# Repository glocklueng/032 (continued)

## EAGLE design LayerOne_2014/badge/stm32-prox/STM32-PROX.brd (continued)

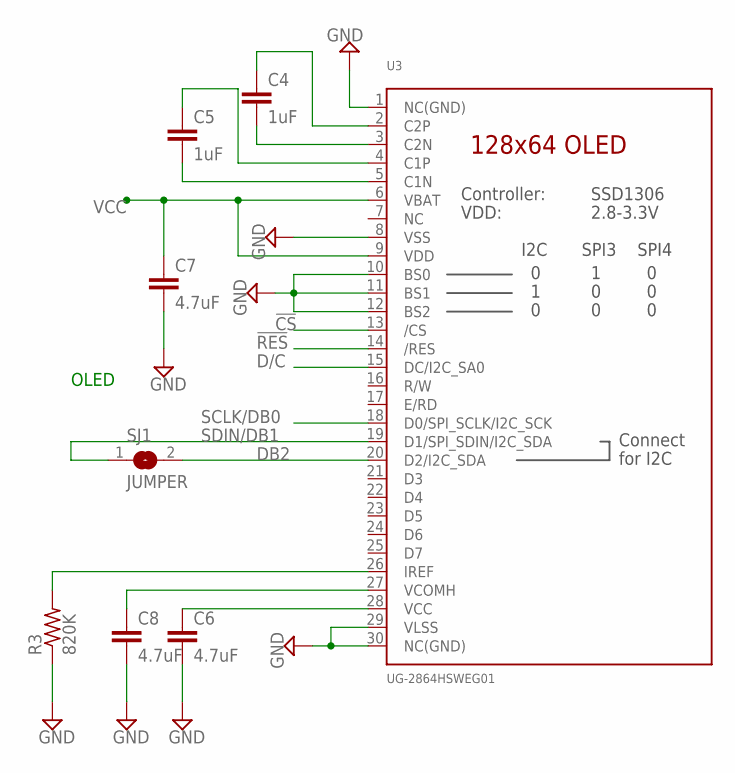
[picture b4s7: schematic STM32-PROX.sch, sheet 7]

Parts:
C4, C5: 1uF; 0805; MPN CC0805ZRY5V8BB105; DIGIKEY 311-1358-1-ND
C6, C7, C8: 4.7uF; 0805; MPN CL21A475KOFNNNE; DIGIKEY 1276-1065-1-ND
R3: 820K; RLC_0603; MPN RC0603JR-07820KL; DIGIKEY 311-820KGRTR-ND
SJ1: JUMPER; SOLDERJUMPER_REFLOW; MPN NONE
U3: UG-2864HSWEG01; MICROBUILDER_UG-2864HSWEG01_0.96IN_WRAPAROUND; PARTNO *

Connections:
!CS: U3.13 (/CS); also elsewhere on the board
!RES: U3.14 (/RES); also elsewhere on the board
D/C: U3.15 (DC/I2C_SA0); also elsewhere on the board
DB2: SJ1.2, U3.20 (D2/I2C_SDA)
GND: C6.2, C7.2, C8.2, R3.1, U3.1 (NC(GND)), U3.8 (VSS), U3.10 (BS0), U3.11 (BS1), U3.12 (BS2), U3.29 (VLSS), U3.30 (NC(GND)); also elsewhere on the board
unnamed: C4.1, U3.2 (C2P)
unnamed: C4.2, U3.3 (C2N)
unnamed: C5.1, U3.4 (C1P)
unnamed: C5.2, U3.5 (C1N)
unnamed: C8.1, U3.27 (VCOMH)
unnamed: C6.1, U3.28 (VCC)
unnamed: R3.2, U3.26 (IREF)
SCLK/DB0: U3.18 (D0/SPI_SCLK/I2C_SCK); also elsewhere on the board
SDIN/DB1: SJ1.1, U3.19 (D1/SPI_SDIN/I2C_SDA); also elsewhere on the board
VCC: C7.1, U3.6 (VBAT), U3.9 (VDD); also elsewhere on the board

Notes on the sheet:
OLED

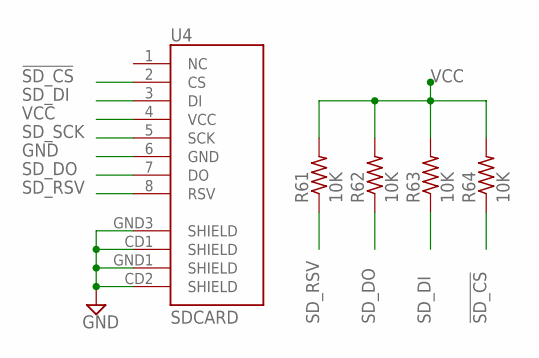
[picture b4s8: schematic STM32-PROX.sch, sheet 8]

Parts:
R61, R62, R63, R64: 10K; RLC_0603; MPN RMCF0603JT10K0; DIGIKEY RMCF0603JT10K0CT-ND
U4: SDCARD; MICRO-SD-SOCKET-PP; PARTNO *

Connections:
!SD_CS: R64.1, U4.2 (CS); also elsewhere on the board
GND: U4.6 (GND), U4.CD1 (SHIELD), U4.CD2 (SHIELD), U4.GND1 (SHIELD), U4.GND3 (SHIELD); also elsewhere on the board
SD_DI: R63.1, U4.3 (DI); also elsewhere on the board
SD_DO: R62.1, U4.7 (DO); also elsewhere on the board
SD_RSV: R61.1, U4.8 (RSV)
SD_SCK: U4.5 (SCK); also elsewhere on the board
VCC: R61.2, R62.2, R63.2, R64.2, U4.4 (VCC); also elsewhere on the board

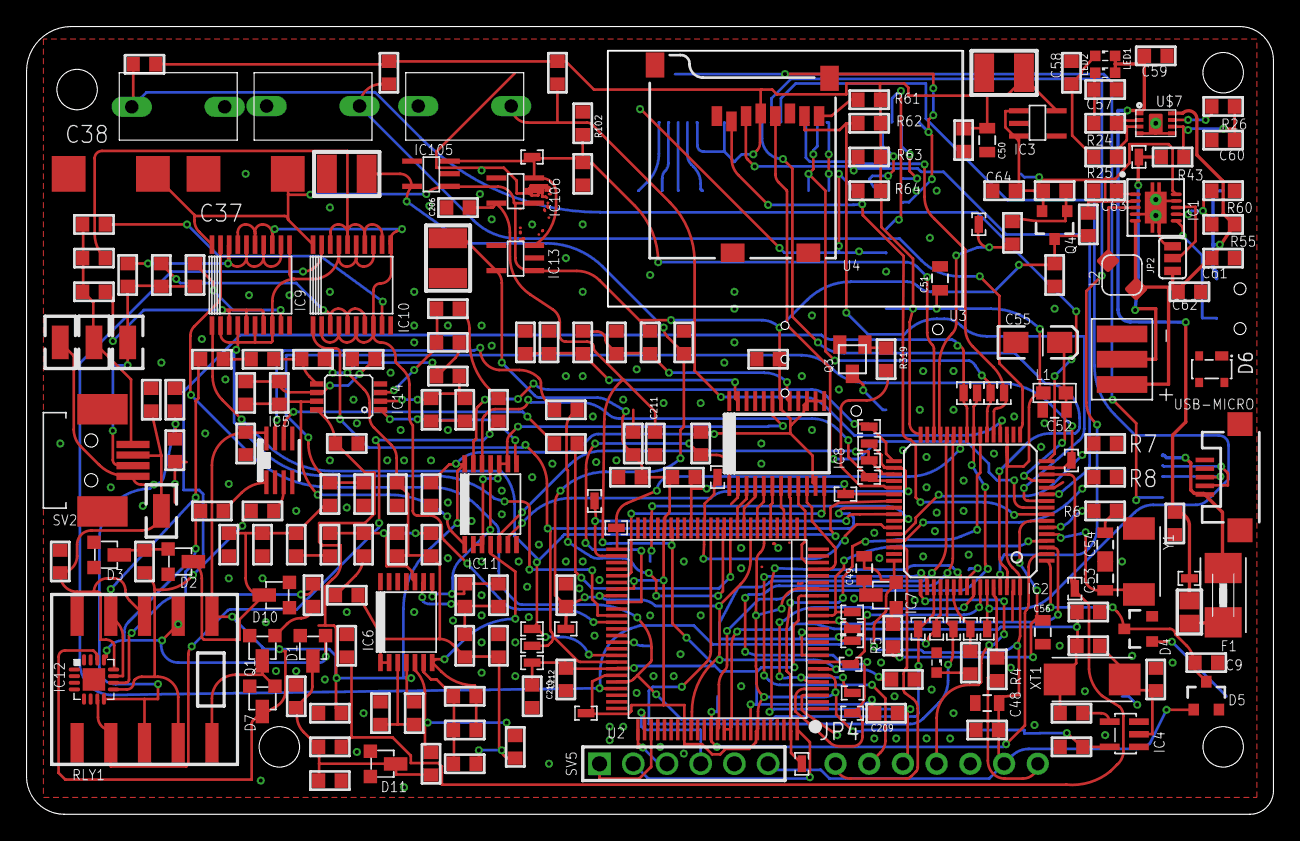
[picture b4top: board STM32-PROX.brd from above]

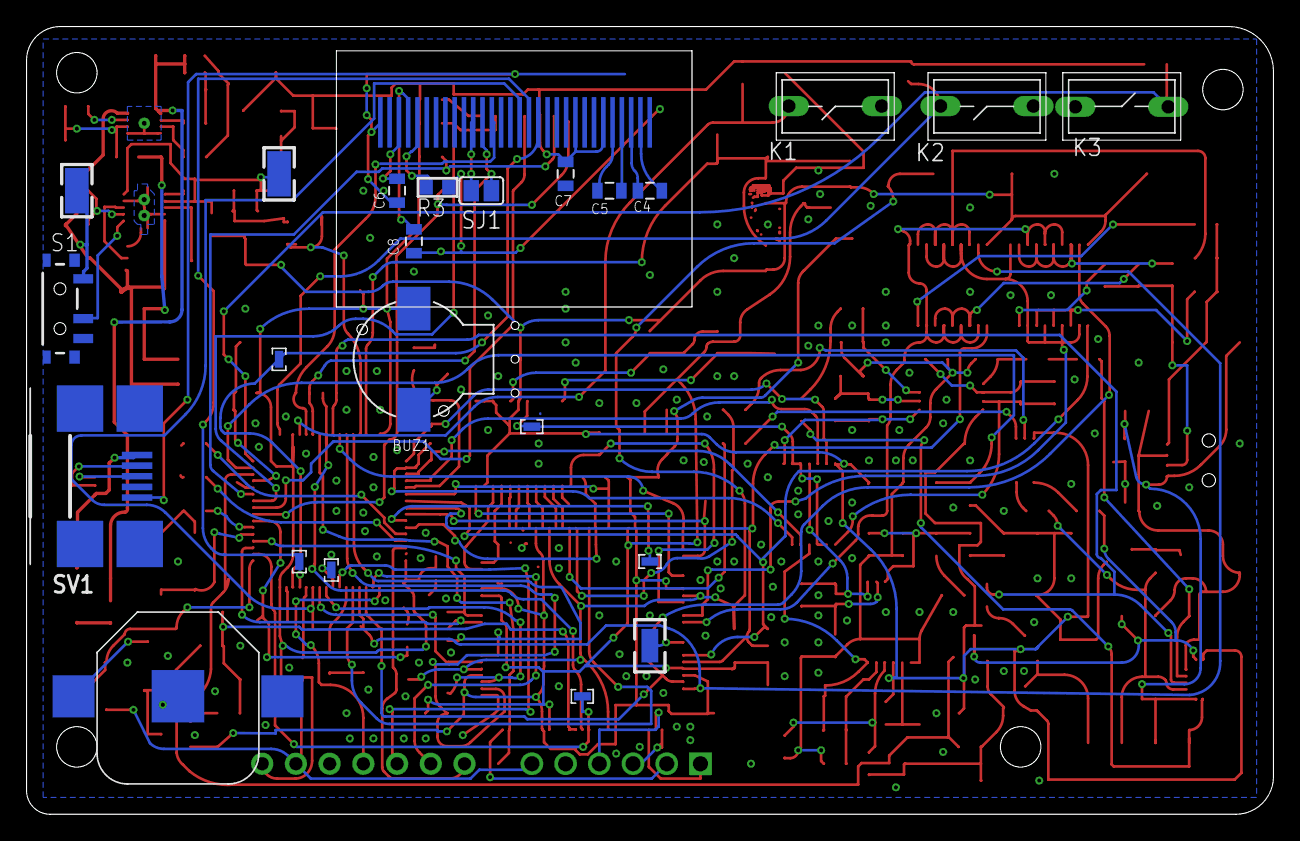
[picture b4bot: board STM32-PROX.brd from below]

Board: 2 copper layers, 94.0 x 59.4 mm, 250 parts (23 on the bottom side), 163 nets.

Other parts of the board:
U$1, U$2, U$4, U$6: STAND-OFF-TIGHT
U$11, U$12, U$13: L1LOGO

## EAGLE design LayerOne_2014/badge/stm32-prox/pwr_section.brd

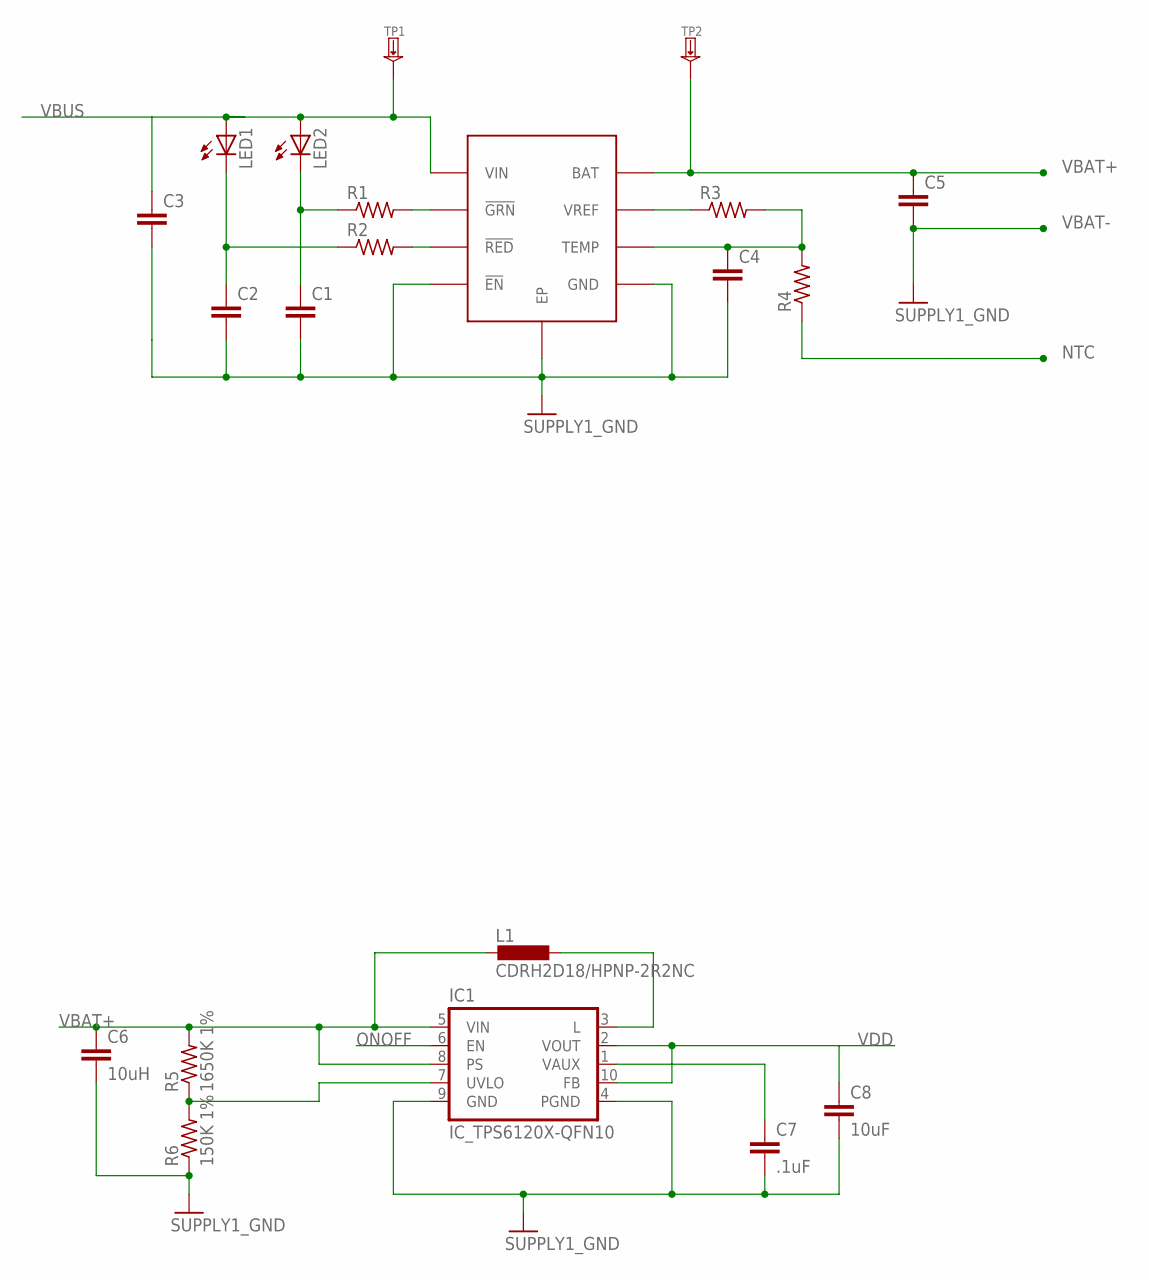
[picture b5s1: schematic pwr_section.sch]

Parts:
C1, C2, C3, C4, C5: SPARKFUN_CAP0603-CAP; SPARKFUN_0603-CAP
C6: 10uH; SPARKFUN_0603-CAP
C7: .1uF; SPARKFUN_0603-CAP
C8: 10uF; SPARKFUN_0603-CAP
IC1: IC_TPS6120X-QFN10; QFN-10
L1: CDRH2D18/HPNP-2R2NC; CDRH2D18
LED1, LED2: LED_LEDCHIP-LED0603; LED_CHIP-LED0603
R1, R2, R3, R4: RCL_R-US_R0603; RCL_R0603
R5: 1650K 1%; RCL_R0603
R6: 150K 1%; RCL_R0603
TP1, TP2: --MERGED_TESTPADKEYSTONE-SMD; --MERGED_KEYSTONE-SMD-TESTPOINT-5015
U$1: MC34674; UDFN-EP

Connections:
GND: C1.2, C2.2, C3.2, C4.2, C6.2, R6.1, U$1.4 (!EN), U$1.5 (GND), U$1.9 (EP)
unnamed: C1.1, LED2.C, R1.1
unnamed: R1.2, U$1.2 (!GRN)
unnamed: C2.1, LED1.C, R2.1
unnamed: R2.2, U$1.3 (!RED)
unnamed: C7.1, IC1.1 (VAUX)
unnamed: IC1.3 (L), L1.P$2 (2)
unnamed: R3.1, U$1.7 (VREF)
unnamed: C4.1, R3.2, R4.2, U$1.6 (TEMP)
unnamed: IC1.7 (UVLO), R5.1, R6.2
NTC: R4.1
ONOFF: IC1.6 (EN)
PGND: C7.2, C8.2, IC1.4 (PGND), IC1.9 (GND)
VBAT+: C5.1, C6.1, IC1.5 (VIN), IC1.8 (PS), L1.P$1 (1), R5.2, TP2.1, U$1.8 (BAT)
VBAT-: C5.2
VBUS: C3.1, LED1.A, LED2.A, TP1.1, U$1.1 (VIN)
VDD: C8.1, IC1.2 (VOUT), IC1.10 (FB)

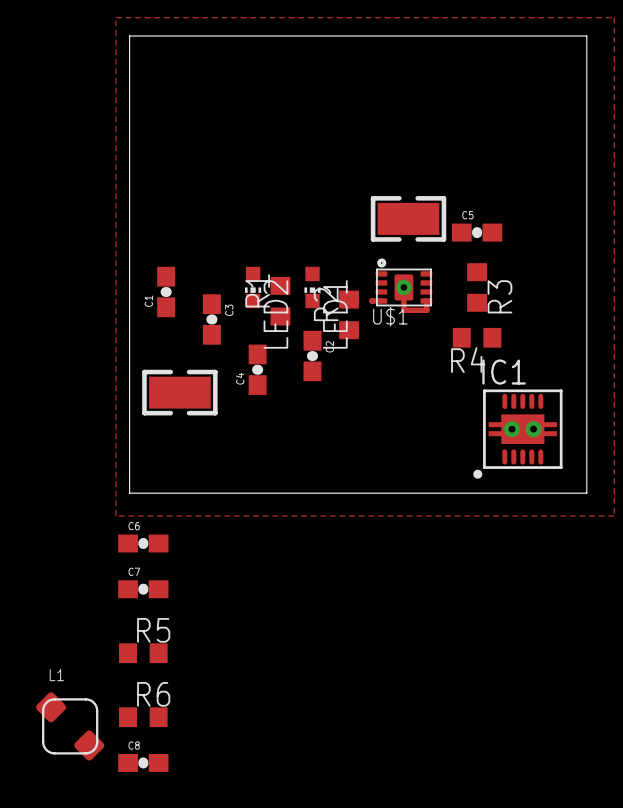
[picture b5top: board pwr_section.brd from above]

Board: 2 copper layers, 25.4 x 25.4 mm, 21 parts (0 on the bottom side), 14 nets.

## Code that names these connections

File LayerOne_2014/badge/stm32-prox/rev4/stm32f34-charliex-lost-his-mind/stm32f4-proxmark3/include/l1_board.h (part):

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
// SPI PINS ARM->FPGA (PROGRAMS & CONFIGURES FPGA)
#define FPGA_DOUT_PORT                  GPIOC
#define FPGA_DOUT_PIN                   GPIO_Pin_11				//output ( reconfigure this to be PCK0)

#define	FPGA_DIN_PORT			GPIOA
#define FPGA_DIN_PIN                    GPIO_Pin_9				//output

#define	FPGA_CCLK_PORT			GPIOA
#define FPGA_CCLK_PIN                   GPIO_Pin_8				//output

#define	FPGA_NPROGRAM_PORT		GPIOA
#define FPGA_NPROGRAM_PIN               GPIO_Pin_7				//output


//OLED
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// Switches

#if BOARD_REVISION == 3
#define SW_K1_PORT                     GPIOB
#else
#define SW_K1_PORT                     GPIOA
#endif

#define SW_K2_PORT                     GPIOA
#define SW_K3_PORT                     GPIOA

#define	RCC_APB2Periph_GPIO_SW		   RCC_APB2Periph_GPIOA
#if BOARD_REVISION == 3
#define SW_K1_PIN                      GPIO_Pin_9				// input, pulldown
#else
#define SW_K1_PIN                      GPIO_Pin_4				// input, pulldown
#endif

#define SW_K2_PIN                      GPIO_Pin_3				// input, pulldown
#define SW_K3_PIN                      GPIO_Pin_2				// input, pulldown

// USB
#if BOARD_REVISION == 3
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#define GPIO_SW_PORTSOURCE            GPIO_PortSourceGPIOA      		// PA

#if BOARD_REVISION == 3
#define GPIO_SW_K1_PINSOURCE          GPIO_PinSource9     			// PB9
#define GPIO_SW_K2_PINSOURCE   	      GPIO_PinSource3     			// PA4
#else
#define GPIO_SW_K1_PINSOURCE          GPIO_PinSource4     			// PA4
#define GPIO_SW_K2_PINSOURCE   	      GPIO_PinSource2     			// PA4
#endif

#define GPIO_SW_K1_EXTI_Line          EXTI_Line0          

// Ampl Lo/Hi
#define AMPL_HI_PIN                    GPIO_Pin_1				// input analog
#define AMPL_LO_PIN                    GPIO_Pin_0				// input analog

#define ADC_AIN_CHANNEL                ADC_Channel_1             		// PA1

#ifdef CS_PIN
#define GPIOA_OUTPUTS_2MHZ_PP_MASK		( CS_PIN | FPGA_NPROGRAM_PIN |SDIN_DB1_PIN | SCLK_DB0_PIN )
#else
#define GPIOA_OUTPUTS_2MHZ_PP_MASK		( FPGA_NPROGRAM_PIN |SDIN_DB1_PIN | SCLK_DB0_PIN )
#endif

#if BOARD_REVISION == 3
#define GPIOA_OUTPUTS_50MHZ_PP_MASK		( FPGA_DOUT_PIN  | FPGA_DIN_PIN | FPGA_CCLK_PIN | SDIN_DB1_PIN | SCLK_DB0_PIN )
#else
#define GPIOA_OUTPUTS_50MHZ_PP_MASK		( FPGA_DOUT_PIN  | FPGA_DIN_PIN | FPGA_CCLK_PIN | USB_DISCONNECT_PIN   | SDIN_DB1_PIN | SCLK_DB0_PIN )
#endif

//#define GPIOA_OUTPUTS_50MHZ_OD_MASK		( USB_DISCONNECT_PIN )
#define GPIOA_INPUT_FLOAT_MASK			( SW_K3_PIN  )
#if BOARD_REVISION == 3
#define GPIOA_INPUT_PULLDOWN_MASK		(  SW_K2_PIN  )
#else
#define GPIOA_INPUT_PULLDOWN_MASK		( SW_K1_PIN | SW_K2_PIN )
#endif
#define GPIOA_ANALOG_MASK			( AMPL_HI_PIN | AMPL_LO_PIN  )
#define GPIOA_DEFAULT_LOW_MASK			( GPIOA_OUTPUTS_2MHZ_PP_MASK | GPIOA_OUTPUTS_50MHZ_PP_MASK )

/* End Section GPIOA */
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#	define MUXSEL_PORT              GPIOB
#endif

#define	MUXSEL_HIPKD_PORT		MUXSEL_PORT
#define	MUXSEL_LOPKD_PORT		MUXSEL_PORT

#define	MUXSEL_HIRAW_PORT		GPIOB
#define	MUXSEL_LORAW_PORT		GPIOB



#if BOARD_REVISION == 3
#define MUXSEL_HIPKD_PIN                GPIO_Pin_9			        //output
#define MUXSEL_LOPKD_PIN                GPIO_Pin_8			        //output
#else
#define MUXSEL_HIPKD_PIN                GPIO_Pin_15			        //output
#define MUXSEL_LOPKD_PIN                GPIO_Pin_14			        //output
#endif


#if BOARD_REVISION == 3
//PORTB
#define MUXSEL_HIRAW_PIN                GPIO_Pin_2			        //output
#define MUXSEL_LORAW_PIN                GPIO_Pin_1			        //output
#else
#define MUXSEL_HIRAW_PIN                GPIO_Pin_13			        //output
#define MUXSEL_LORAW_PIN                GPIO_Pin_12			        //output
#endif

// FPGA Power On
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#define FPGAON_PIN                      GPIO_Pin_11				//output

// USB Power On
#define	NVDD_ON_PORT			GPIOB
#define NVDD_ON_PIN                     GPIO_Pin_10				//output

// FPGA DONE
#define FPGA_DONE_PORT                  GPIOB
#define FPGA_DONE_PIN                   GPIO_Pin_0				// input


// OLED
#if BOARD_REVISION == 3
#define OLED_PORT                	GPIOB
#define RES_PIN                         GPIO_Pin_8               		// inverted output
#define DC_PIN                          GPIO_Pin_7				// output
#else
#define OLED_PORT                	GPIOB
#define OLED_CS_PORT                	GPIOB
#define CS_PIN                          GPIO_Pin_9               		// inverted output
#define RES_PIN                         GPIO_Pin_8               		// inverted output
#define DC_PIN                          GPIO_Pin_7				// output
#endif

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#if BOARD_REVISION == 3

#define SSP_PORT	                GPIOB
#define SSP_DIN_PORT			GPIOB
#define SSP_DIN_PIN                     GPIO_Pin_15				// input(OUTPUT)	
#define SSP_DOUT_PORT			GPIOB
#define SSP_DOUT_PIN                    GPIO_Pin_14				// output
#define SSP_CLK_PORT			GPIOB
#define SSP_CLK_PIN                     GPIO_Pin_13			        // input
#define SSP_FRAME_PORT			GPIOB
#define SSP_FRAME_PIN                   GPIO_Pin_12				// input

#else

#define SSP_PORT	                GPIOB
#define SSP_DIN_PORT			GPIOB

#define SSP_DIN_PIN                     GPIO_Pin_6				// input(OUTPUT)	
#define SSP_DOUT_PORT			GPIOB
#define SSP_DOUT_PIN                    GPIO_Pin_5				// output
#define SSP_CLK_PORT			GPIOB
#define SSP_CLK_PIN                     GPIO_Pin_2			        // input
#define SSP_FRAME_PORT			GPIOB
#define SSP_FRAME_PIN                   GPIO_Pin_1				// input

#endif

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//@todo: USB_DISCONNECT_PIN
#if BOARD_REVISION == 3

#define GPIOB_OUTPUTS_2MHZ_PP_MASK		( DC_PIN | RES_PIN | USB_DISCONNECT_PIN |				\
						CS_PIN | FPGAON_PIN  | MUXSEL_HIRAW_PIN | MUXSEL_LORAW_PIN )
#else
#define GPIOB_OUTPUTS_2MHZ_PP_MASK		( DC_PIN | RES_PIN | 				\
						CS_PIN | FPGAON_PIN  | MUXSEL_HIPKD_PIN | 	\
						MUXSEL_LOPKD_PIN |MUXSEL_HIRAW_PIN | MUXSEL_LORAW_PIN )
#endif

//#define GPIOB_OUTPUTS_10MHZ_PP_MASK		( )
#define GPIOB_OUTPUTS_50MHZ_PP_MASK		( NVDD_ON_PIN  )
//#define GPIOB_OUTPUTS_50MHZ_OD_MASK		( USB_DISCONNECT_PIN )

//#define GPIOB_INPUT_FLOAT_MASK		( SSP_CLK_PIN )
#define GPIOB_INPUT_PULLUP_MASK			( FPGA_DONE_PIN ) 

#if BOARD_REVISION == 3
#define GPIOB_INPUT_PULLDOWN_MASK		( SW_K1_PIN | SSP_FRAME_PIN | SSP_DIN_PIN |SSP_DOUT_PIN | SSP_CLK_PIN ) // Might want to make these float
#else
#define GPIOB_INPUT_PULLDOWN_MASK		( SSP_FRAME_PIN | SSP_DIN_PIN |SSP_DOUT_PIN | SSP_CLK_PIN ) // Might want to make these float
#endif

//#define GPIOB_ANALOG_MASK			( )
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#define MOSI_PORT                      GPIOC
#define MOSI_PIN                       GPIO_Pin_14				// output to fpga

#define SPCK_PORT                      GPIOC
#define SPCK_PIN                       GPIO_Pin_13				// output to fpga

#define NCS_PORT                       GPIOC
#define NCS_PIN                        GPIO_Pin_12				// output to fpga

#if BOARD_REVISION != 3
// Output Enables (these aren't supposed to be on the ARM) !!
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#endif

// FPGA_NINIT
#define FPGA_NINIT_PORT                 GPIOC
#define FPGA_NINIT_PIN                  GPIO_Pin_7			        // input, pullup

// Speaker
#define SPEAKER_PORT                    GPIOC
#define SPEAKER_PIN                     GPIO_Pin_6                              // output

// Relay control
#define RELAY_PORT                      GPIOC
#define RELAY_PIN                       GPIO_Pin_5

// PCKO
#define PCK0_PORT			GPIOC	
#define PCK0_PIN			GPIO_Pin_4				// output clock for FPGA/SSP 24Mhz clock

// SD-CARD
#define SDCARD_PORT                    GPIOC
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#define SDCS_PIN                       GPIO_Pin_0				// output

#if BOARD_REVISION == 3
#define GPIOC_OUTPUTS_2MHZ_PP_MASK		(MUXSEL_HIPKD_PIN  | MUXSEL_LOPKD_PIN | RELAY_PIN |SDDO_PIN | SDCS_PIN)
#else
#define GPIOC_OUTPUTS_2MHZ_PP_MASK		(   |SDDO_PIN | SDCS_PIN)

#endif

#define GPIOC_OUTPUTS_10MHZ_PP_MASK		( SPEAKER_PIN | SDSCK_PIN | NCS_PIN | MOSI_PIN |SPCK_PIN )
#define GPIOC_OUTPUTS_50MHZ_PP_MASK		( PCK0_PIN   )

#if BOARD_REVISION == 3
#define GPIOC_INPUT_FLOAT_MASK          ( SDDI_PIN | MISO_PIN )
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#define GPIOC_INPUT_FLOAT_MASK          ( OE4_PIN | OE3_PIN | OE2_PIN | OE1_PIN | SDDI_PIN | MISO_PIN )
#endif

#define GPIOC_INPUT_PULLUP_MASK			( FPGA_NINIT_PIN )

#if BOARD_REVISION == 3
#define GPIOC_ANALOG_MASK				( GPIO_Pin_4 | GPIO_Pin_3 )
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#define LED_PORT                        GPIOD
#define LED_PIN                         GPIO_Pin_2                              // output
#define RCC_APB2Periph_GPIO_LED         RCC_APB2Periph_GPIOD      		// PD
// PD0/PD1 XTAL



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
// aliases for proxmark3

#define				GPIO_MUXSEL_HIPKD_PIN	MUXSEL_HIPKD_PIN
#define				GPIO_MUXSEL_LOPKD_PIN	MUXSEL_LOPKD_PIN
#define				GPIO_MUXSEL_HIRAW_PIN	MUXSEL_HIRAW_PIN
#define				GPIO_MUXSEL_LORAW_PIN	MUXSEL_LORAW_PIN

#define				GPIO_MUXSEL_HIPKD_PORT	MUXSEL_HIPKD_PORT
#define				GPIO_MUXSEL_LOPKD_PORT	MUXSEL_LOPKD_PORT
#define				GPIO_MUXSEL_HIRAW_PORT	MUXSEL_HIRAW_PORT
#define				GPIO_MUXSEL_LORAW_PORT	MUXSEL_LORAW_PORT

// only one led
#define				GPIO_LED_A_PIN			LED_PIN
#define				GPIO_LED_B_PIN			LED_PIN
#define				GPIO_LED_C_PIN			LED_PIN
#define				GPIO_LED_D_PIN			LED_PIN

#define				GPIO_LED_A_PORT			LED_PORT
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
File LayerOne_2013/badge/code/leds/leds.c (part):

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
	// PORTS CONFIGURATION
	// Initial value PORTA.DIR       = 0x00; // CH2, CH1, 1V, K1, K2, K3, K4, REF
	PORTA.PIN1CTRL  = MENUPULL; // Pull up or pull down on pin PA1
	PORTA.PIN2CTRL  = 0x18; // Pull up on pin PA2
	PORTA.PIN3CTRL  = 0x18; // Pull up on pin PA3
	PORTA.PIN4CTRL  = 0x18; // Pull up on pin PA4
		PORTA.PIN5CTRL  = 0x07; // Input Disable on pin PA5
	PORTA.PIN6CTRL  = 0x07; // Input Disable on pin PA6
	PORTA.PIN7CTRL  = 0x07; // Input Disable on pin PA7
	PORTA.INTCTRL   = 0x02; // PORTA will generate medium level interrupts
	PORTA.INT0MASK  = 0x1E; // PA4, PA3, PA2, PA1 will be the interrupt 0 sources
	PORTB.DIR       = 0x0B; // RES, AWG, D/C, R/W
   
	// Initial Value PORTB.OUT       = 0x00; //
	// Initial Value PORTC.DIR       = 0x00; // LOGIC
	PORTC.INT0MASK  = 0x01; // PC0 (SDA) will be the interrupt 0 source
	PORTC.INT1MASK  = 0x80; // PC7 (SCK) will be the interrupt 1 source
 
	PORTD.DIR		= 0xFF;  // LEDs
	PORTCFG.MPCMASK = 0xFF; // Configure all pins on PORTD the same way
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	PORTD.DIR       = 0x1F; // USB, EXT, GREEN, TX, RX, CLK, RED
	PORTD.OUT       = 0x04; // LCD voltage off
	PORTE.DIR       = 0x09; // TX, RX, RTS (input), CTS (power external board)
	PORTE.PIN1CTRL  = 0x18; // Pull up on pin PE1 (RTS)
	PORTE.OUT       = 0x01; // Power to external board
	PORTCFG.VPCTRLA = 0x41; // VP1 Map to PORTE, VP0 Map to PORTB
	//PORTCFG.VPCTRLB = 0x32; // VP3 Map to PORTD, VP2 Map to PORTC
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
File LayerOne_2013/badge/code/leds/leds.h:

#ifndef _RF_BLINKY_H_
#define _RF_BLINKY_H_ ( 1 )


#define __AVR_ATxmega32A4__

// includes

#include <avr/io.h>
#include <util/delay.h>
#include <avr/interrupt.h>
#include <avr/sfr_defs.h>

#include <math.h> 
#include <avr/eeprom.h>
#include <avr/sleep.h>
#include <avr/power.h>
#include <avr/pgmspace.h>

#include <stdlib.h>
#include <string.h>
#include <math.h>

// typedefs

typedef unsigned char uchar;
typedef unsigned int uint;

// structures

// defines
#define LEDS_HEIGHT ( 48 )
#define LEDS_WIDTH ( 1 )

#define NUM_TLC5947 ( 2 )

#define bit_set(reg, bit) reg |= 1 << bit 
#define bit_clr(reg, bit) reg &= ~(1 << bit) 

#ifndef TWO_PI
#define TWO_PI                 ( 6.283185307f )
#endif


#define DATPIN		( PIN0_bp )    //    SIN
#define CLKPIN		( PIN2_bp )
#define BLANKPIN	( PIN4_bp ) 
#define LATPIN		( PIN5_bp )

#define SIN_PIN     ( PIN0_bm ) /// PC0
#define SCLK_PIN	( PIN2_bm ) /// PC1
#define BLANK_PIN	( PIN4_bm ) /// PC2
#define XLAT_PIN    ( PIN5_bm ) /// PC3a


extern uint16_t LEDChannels[(NUM_TLC5947)];
extern unsigned char brightnessShift;


// prototypes


void Clear(unsigned short val);

// TLC
void WriteLEDArray(unsigned int count);
void LEDscan(int red, float degreeoffset,unsigned int count);
void LEDscan2(int red, float degreeoffset,unsigned int count);
void LEDscan3(int red, float degreeoffset,unsigned int count);
void LED_Init(void);
void LEDscan2Add(int red, float degreeoffset,unsigned int count);

#endif
